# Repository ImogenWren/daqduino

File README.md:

# DAQduino
 DAQ Arduino, Voltage and Current Data Aquisition Unit.
 
 ## Goal 
 DAQduino is a standalone DAQ device capable of logging data from 
a few sources to a CSV file on an SD card, sending data in realtime
to a PC, and displaying the data for a particular sensor on a screen
 
 ## Using Arduino for Data Aquisition
 
 _There are several different methods that could be used for basic Data Aquisition tasks with just a few sensors that are easy to integrate with the Arduino Platform._
 
 1. Arduino streams serial data in CSV format. 
    - Use Putty/Kitty to record log
    - Python program to log to file
    - LabVIEW program to log to file

 2. Arduino streams data in JSON format.
    - Use Putty/Kitty and export data later
    - Python to log to file

3. Arduino waits for serial message to release data packet
    - Putty/Kitty to record log
    - LabVIEW for full DAQ implementation
    - Python for basic IO Interface - command line?
    - Python Desktop App

4. Full Integration between arduino and desktop software.

### Functions:
 - 10v, 12v and 24v outputs for sensor power
 - 0 - 10v analog input
 - 0 - 5v TTL IO
 - 4 - 20mA input
 - OLED Screen
 - Encoder Control
 - Basic Scaling

#### Stretch Goals:
 - 0 - 10 v output
 - 0 - 20 mA output

### Communications:
- Serial Data
- Labveiw Integration?

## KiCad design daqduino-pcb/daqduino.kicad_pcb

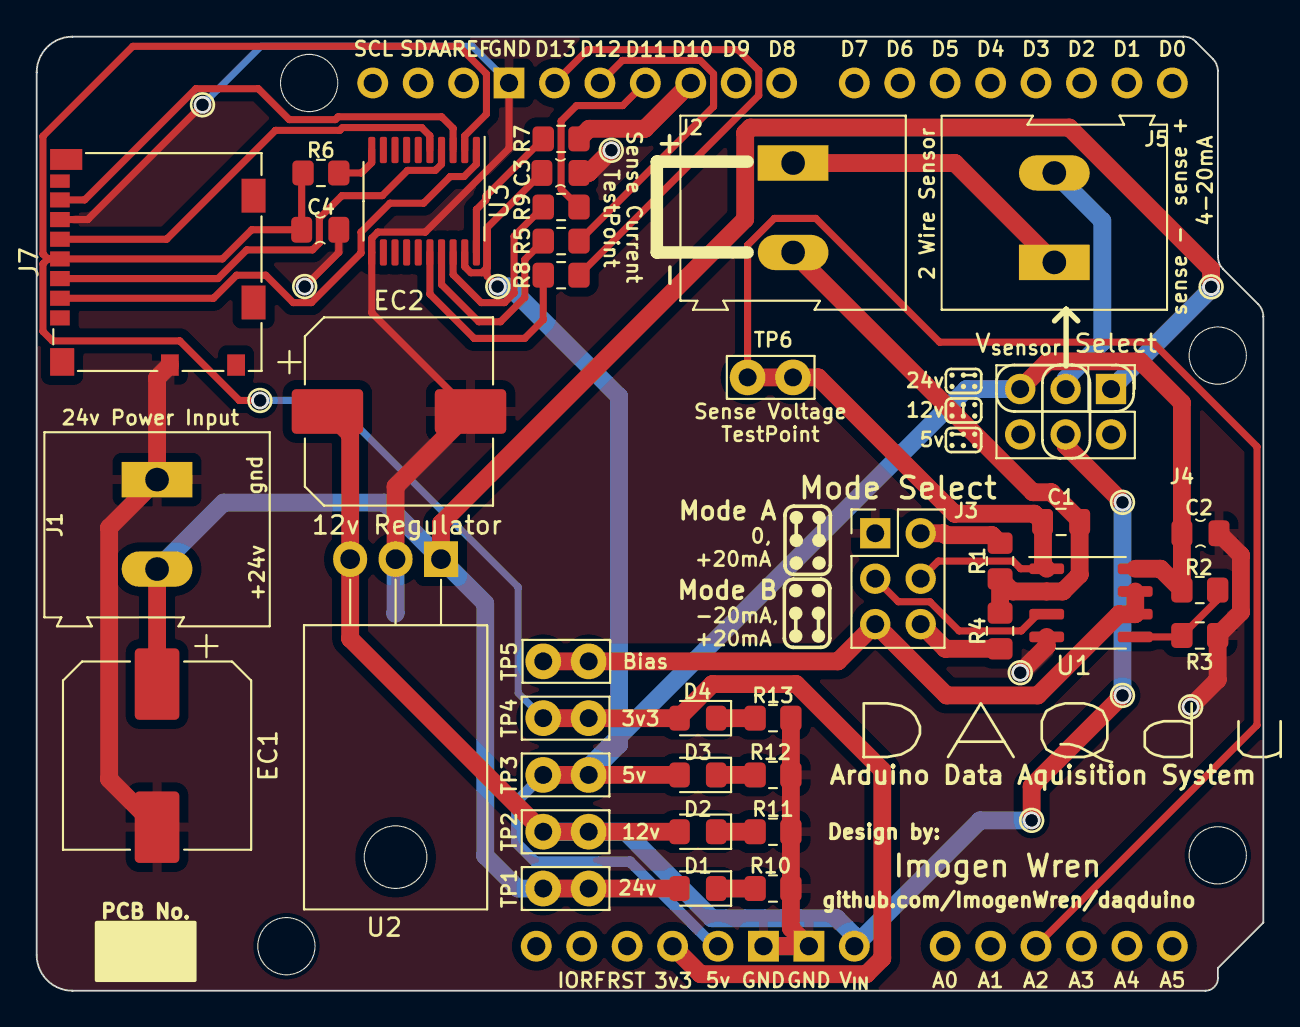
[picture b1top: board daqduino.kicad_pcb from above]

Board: 2 copper layers, 68.6 x 53.3 mm, 39 parts (0 on the bottom side), 31 nets.

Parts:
C1: 470n; C_0805_2012Metric_Pad1.18x1.45mm_HandSolder
C2, C3, C4: 100n; C_0805_2012_HandSolder_kawaii
D1: red; D_0805_2012Metric_Pad1.15x1.40mm_HandSolder
D2: yellow; D_0805_2012Metric_Pad1.15x1.40mm_HandSolder
D3: green; D_0805_2012Metric_Pad1.15x1.40mm_HandSolder
D4: blue; D_0805_2012Metric_Pad1.15x1.40mm_HandSolder
EC1, EC2: 100u; CP_Elec_10x10
J1: 24v Power Input; TerminalBlock_Altech_AK300-2_P5.00mm
J2: Sense Current; TerminalBlock_Altech_AK300-2_P5.00mm
J3: Mode Select; PinHeader_2x03_P2.54mm-alt-pin-no
J4: V_{sensor} Select; PinHeader_2x03_P2.54mm-alt-pin-no
J5: 2 Wire Sensor; TerminalBlock_Altech_AK300-2_P5.00mm
J7: Micro SD Card; microSD_HC_Molex_104031-0811
R1: 220r; R_0805_2012Metric_Pad1.20x1.40mm_HandSolder
R2, R3, R10: 10k; R_0805_2012Metric_Pad1.20x1.40mm_HandSolder
R4: 100r; R_0805_2012Metric_Pad1.20x1.40mm_HandSolder
R5, R6, R7, R8, R9: 3k3; R_0805_2012Metric_Pad1.20x1.40mm_HandSolder
R11: 4k7; R_0805_2012Metric_Pad1.20x1.40mm_HandSolder
R12: 2k2; R_0805_2012Metric_Pad1.20x1.40mm_HandSolder
R13: 1k; R_0805_2012Metric_Pad1.20x1.40mm_HandSolder
TP1: 24v; TestPoint_Bridge_Pitch2.54mm_Drill1.0mm
TP2: 12v; TestPoint_Bridge_Pitch2.54mm_Drill1.0mm
TP3: 5v; TestPoint_Bridge_Pitch2.54mm_Drill1.0mm
TP4: 3v3; TestPoint_Bridge_Pitch2.54mm_Drill1.0mm
TP5: Bias; TestPoint_Bridge_Pitch2.54mm_Drill1.0mm
TP6: Sense Voltage; TestPoint_Bridge_Pitch2.54mm_Drill1.0mm
U1: LM358; SOIC-8_3.9x4.9mm_P1.27mm
U2: 12v Regulator; TO-220-3_Horizontal_TabDown
U3: TXS0108EPW; TSSOP-20_4.4x6.5mm_P0.65mm
XA1: Arduino_Uno_R3_Shield-simple

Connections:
/3V3_BUS: C4.1, D4.2 (A), J7.4 (VDD), R6.2, TP4.1, U3.2 (VCCA), XA1.3V3 (3.3V)
/5V_BUS: C2.1, C3.1, D3.2 (A), J4.3, R2.2, TP3.1, U1.8 (V+), U3.19 (VCCB), XA1.5V1 (5V)
/12V_BUS: D2.2 (A), EC2.1, J4.5, TP2.1, U2.3 (OUT), XA1.VIN
/24V_BUS: D1.2 (A), EC1.1, J1.2, J4.1, TP1.1, U2.1 (IN)
/BIAS_VOLTAGE: J3.2, U1.3 (+)
/CHIP_SELECT: R7.1, XA1.D10 (D10_CS)
/CLK: J7.5 (CLK), U3.5 (A4)
/CS: J7.2 (DAT3/CD), U3.1 (A1)
/D_{IN}: J7.3 (CMD), U3.4 (A3)
/D_{OUT}: J7.7 (DAT0), U3.3 (A2)
/MISO: R9.1, XA1.D11
/MOSI: R5.1, XA1.D12
/R_SET_A: C1.1, J2.2, R1.2, R4.2, U1.2 (-)
/R_SET_B: C1.2, J3.5, TP6.1, U1.1, XA1.A2
/SCK: R8.1, XA1.D13
/SENSE_CURRENT: J2.1, J5.1
/SENSOR_POWER: J4.2, J5.2
GND: C2.2, C3.2, C4.2, EC1.2, EC2.2, J1.1, J3.1, J7.6 (VSS), J7.9 (SHIELD), R3.1, R10.1, R11.1, R12.1, R13.1, U1.4 (V-), U2.2 (GND), U3.11 (GND), XA1.GND1 (GND), XA1.GND2 (GND), XA1.GND3 (GND)
unnamed: D1.1 (K), R10.2
unnamed: D2.1 (K), R11.2
unnamed: D3.1 (K), R12.2
unnamed: D4.1 (K), R13.2
unnamed: J3.3, TP5.1, U1.6 (-), U1.7
unnamed: J3.4, R4.1
unnamed: J3.6, R1.1
unnamed: R2.1, R3.2, U1.5 (+)
unnamed: R7.2, U3.20 (B1)
unnamed: R9.2, U3.18 (B2)
unnamed: R5.2, U3.17 (B3)
unnamed: R8.2, U3.16 (B4)
unnamed: R6.1, U3.10 (OE)

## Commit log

2023-02-24 khnljkglkuv
2023-04-04 updated foldernames
2023-05-23 Started work on desktop app using python
2023-05-24 working on CLI for DACduino
2023-05-24 vfgfg
2023-05-26 ksdflk
2023-06-02 kjglkjhgkjhgf
2023-06-05 almost finished schematic
2023-06-06 sdfsdf
2023-06-07 started pcb laypouty
2023-06-08 finished PCB design
2023-06-09 sdfs
2023-07-05 oshldgf
2023-07-05 sdfgsdffs
2023-07-06 bdfdfbdb
2023-07-07 sfsdfsd
2023-07-10 got rid of incorrectly names and older files
2023-07-10 aaahahahahahaaa feck sd card not working
2023-07-11 SD CARD TEST LOGGER WORKS! finally
2023-07-12 Finished DAQduino - Firmware V1.0
2023-07-12 changed files
2023-07-13 updating
2023-07-13 small improvements - start function if no SD card after n attempts
